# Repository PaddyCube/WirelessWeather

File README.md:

## Description
Build your own Wireless Weather station. This station includes:
- Temperature
- Humidity
- Pressure
- Rain Level
- Wind Speed
- Wind direction
- Battery monitor

There are three versions available: 
- One uses ESP8622 module and some ATTINYs
- one uses ESP32 and only one ATTINY for wind direction 
- one uses an Arduino Mini together with ATTINY24 for wind direction inside weather station and publish messages by 433 Mhz.

Code and schematics for any solution can be found in corresponding subfolders of folder 'code'

## Operation mode
### ESP8266
Wind speed and rain gets detected by pin change interrupt of ATTINYs. 
There is a power hungry device called WEMOS D1 mini pro, which deep sleeps most time. 
Every few minutes, it wakes up, collect data from other devices by I2C, send everything to your MQTT broker and sleeps again.

### ESP32
Wind speed and rain gets count by ULP co-processor of ESP32 module. Every few minutes, ESP32 wakes from deep sleep, read count values from ULP, power up I2C devices and sends everything to your MQTT broker. Then it sleeps again.

### Arduino Pro Mini
Because ESP devices are pretty power hungry, I wanted to build something more power saving. Therefore, a Arduino Pro Mini is used inside the weather station. Most time it sleeps and count wind and rain by interrupts. Every x minutes, it wakes up, power up I2C devices (BME280 and ATTINY24 for wind direction), reads values and send them using cheap 433MHz module. You find a working example based on ESP8266 module acting as a bridge between 433 Mhz and MQTT, so it receives data over 433MHz and publish them like before using MQTT. 

## Project site
You find all 3D printed parts at Thingiverse 
https://www.thingiverse.com/thing:3718078

A video is here https://youtu.be/xa0Dt5vs0kM

## BOM
This package includes software for the following components
### ESP8266
- 2x ATTINY85 (wind speed, rain and battery level)
- 1x ATTINY24 (wind direction)
- Wemos D1 Mini pro (or other ESP8266 device)
- 1x BME280
- Please find a complete BOM in BOM.txt file

Moreover you need some device to program ATTINYs. This can be done with any Arduino device. There are plenty of tutorials out there.

### ESP32
- 1x ATTINY24 (wind direction, see folder Wireless Weather)
- ESP32 (DOIT DevKit V1 with 30 GPIOs)
- 1x BME280

For further information, please see readme file in ESP32 folder

### Arduino Pro Mini
- 1x Arduino Pro Mini
- 1x ATTINY24 (wind direction)
- 1x BME280
- 1x 433MHz receiver, transmitter pair

You also need some code and device to receive the data and process them further. This can be done with any device, like Arduino, ESP8266, ESP32, Raspberry PI and so on. To get a complete working example, I added some code for ESP8266 (WEMOS D1 mini pro) which
acts as some kind of bridge between 433MHz and MQTT, meaning it receives the data send by Arduino Pro Mini and send them using MQTT protocol.

## Required Software
For ATTINYs, you need this package <br>
https://github.com/SpenceKonde/ATTinyCore <br>
https://github.com/rambo/TinyWire <br>

For ESP8266 and ESP32, I used this one <br>
https://arduino.esp8266.com/stable/package_esp8266com_index.json <br>
https://github.com/knolleary/pubsubclient <br>
https://github.com/adafruit/Adafruit_BME280_Library <br>

When using Arduino Pro mini, you need these packages as well <br>
https://github.com/rocketscream/Low-Power <br>
https://github.com/PaulStoffregen/RadioHead <br>
https://github.com/adafruit/Adafruit_BME280_Library <br>

## License
<br>Copyright (c) 2019 by Patrick Weber  

Private-use only! (you need to ask for a commercial-use)

You should have received a copy of the GNU General Public License
along with this program.  If not, see <http://www.gnu.org/licenses/>.

Private-use only! (you need to ask for a commercial-use)

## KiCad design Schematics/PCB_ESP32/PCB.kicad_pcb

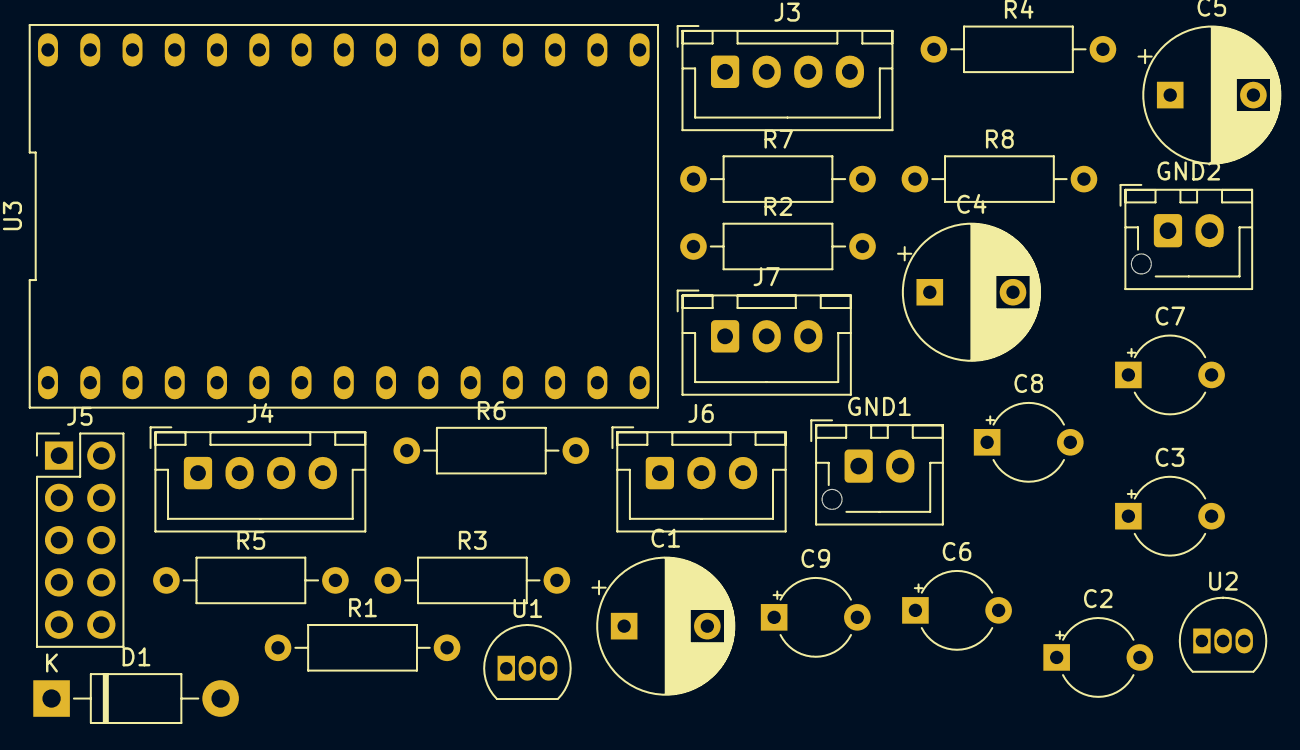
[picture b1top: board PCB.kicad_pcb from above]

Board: 2 copper layers, 28 parts (0 on the bottom side), 12 nets, no tracks yet.

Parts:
C1, C4, C5: 4.7uF; CP_Radial_D8.0mm_P5.00mm
C2, C3, C6, C7: 1uF (ceramic); CP_Radial_Tantal_D4.5mm_P5.00mm
C8, C9: 0.1uF; CP_Radial_Tantal_D4.5mm_P5.00mm
D1: SB 5100; D_DO-41_SOD81_P10.16mm_Horizontal
GND1: Solar VCC; JST_XH_B2B-XH-AM_1x02_P2.50mm_Vertical
GND2: BAT +; JST_XH_B2B-XH-AM_1x02_P2.50mm_Vertical
J3, J4: I2C; JST_XH_B4B-XH-A_1x04_P2.50mm_Vertical
J5: WindVane; PinHeader_2x05_P2.54mm_Vertical
J6: WindSpeed; JST_XH_B3B-XH-A_1x03_P2.50mm_Vertical
J7: Rain; JST_XH_B3B-XH-A_1x03_P2.50mm_Vertical
R1, R2: 4k7; R_Axial_DIN0207_L6.3mm_D2.5mm_P10.16mm_Horizontal
R3, R4: R; R_Axial_DIN0207_L6.3mm_D2.5mm_P10.16mm_Horizontal
R5: 20M; R_Axial_DIN0207_L6.3mm_D2.5mm_P10.16mm_Horizontal
R6, R8: 10M; R_Axial_DIN0207_L6.3mm_D2.5mm_P10.16mm_Horizontal
R7: 5M2; R_Axial_DIN0207_L6.3mm_D2.5mm_P10.16mm_Horizontal
U1: MCP1702-5002E_TO92 5V; TO-92_Inline
U2: MCP1700-3302E_TO92 3.3V; TO-92_Inline
U3: ESP32-WROOM-32; ESP32DevKit

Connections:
GND: C1.2, C2.1, C3.1, C4.2, C5.2, C6.1, C7.2, C8.1, C9.1, GND1.1, GND2.1, J3.2, J4.2, J5.10, J6.2, J7.2, R6.2, R8.2, U1.1, U2.1, U3.1, U3.15
unnamed: C1.1, C2.2, GND1.2, R5.1, U1.2
unnamed: C3.2, C4.1, D1.1, U1.3
unnamed: C5.1, C6.2, D1.2, GND2.2, U2.2
unnamed: C7.1, J3.1, J4.1, J6.3, J7.3, R1.1, R2.1, R3.1, R4.1, U2.3, U3.2
unnamed: C8.2, R5.2, R6.1, U3.6
unnamed: C9.2, R7.2, R8.1, U3.7
unnamed: J3.3, J4.3, R1.2
unnamed: J3.4, J4.4, R2.2
unnamed: J5.5, U3.13
unnamed: J6.1, R3.2, U3.9
unnamed: J7.1, R4.2, U3.8

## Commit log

2019-07-13 Initial Commit
    Initial Commit
2019-07-16 Schematics added
    Kikad Files added, Schematics as PDF
2019-07-20 Schematics Update
    Schematics update, now working I2C Communication. New Code for ATTINYs (less overhead)
2019-08-06 Small fixes, Solar power added
2019-08-06 Pictures and BOM
2019-08-06 Smaller pictures
2019-09-03 ESP32-PCB
    Start of development for ESP32 PCB
2019-09-24 PCB for ESP32
2019-09-24 Create ulp_count.s
    Assembler code for ESP32 ULP co-processor. This code should be able to count pulses of two distinct gpios
2019-09-26 ESP32 Test Code
2019-09-26 Start of eSP32 development
2019-10-13 ESP32 Code complete
2019-11-27 Arduino mini code
2019-12-06 ESP8266 RF receiver code added
2019-12-10 Convert incoming buffer to struct
2019-12-10 Update BOM, Readme, move files
2019-12-12 small changes
2019-12-16 small changes to 433 library
2019-12-17 working example of 433 MHZ transmission
2019-12-29 Arduino pro mini final
2020-01-07 Schematics for ESP32
2020-04-20 added STL files
